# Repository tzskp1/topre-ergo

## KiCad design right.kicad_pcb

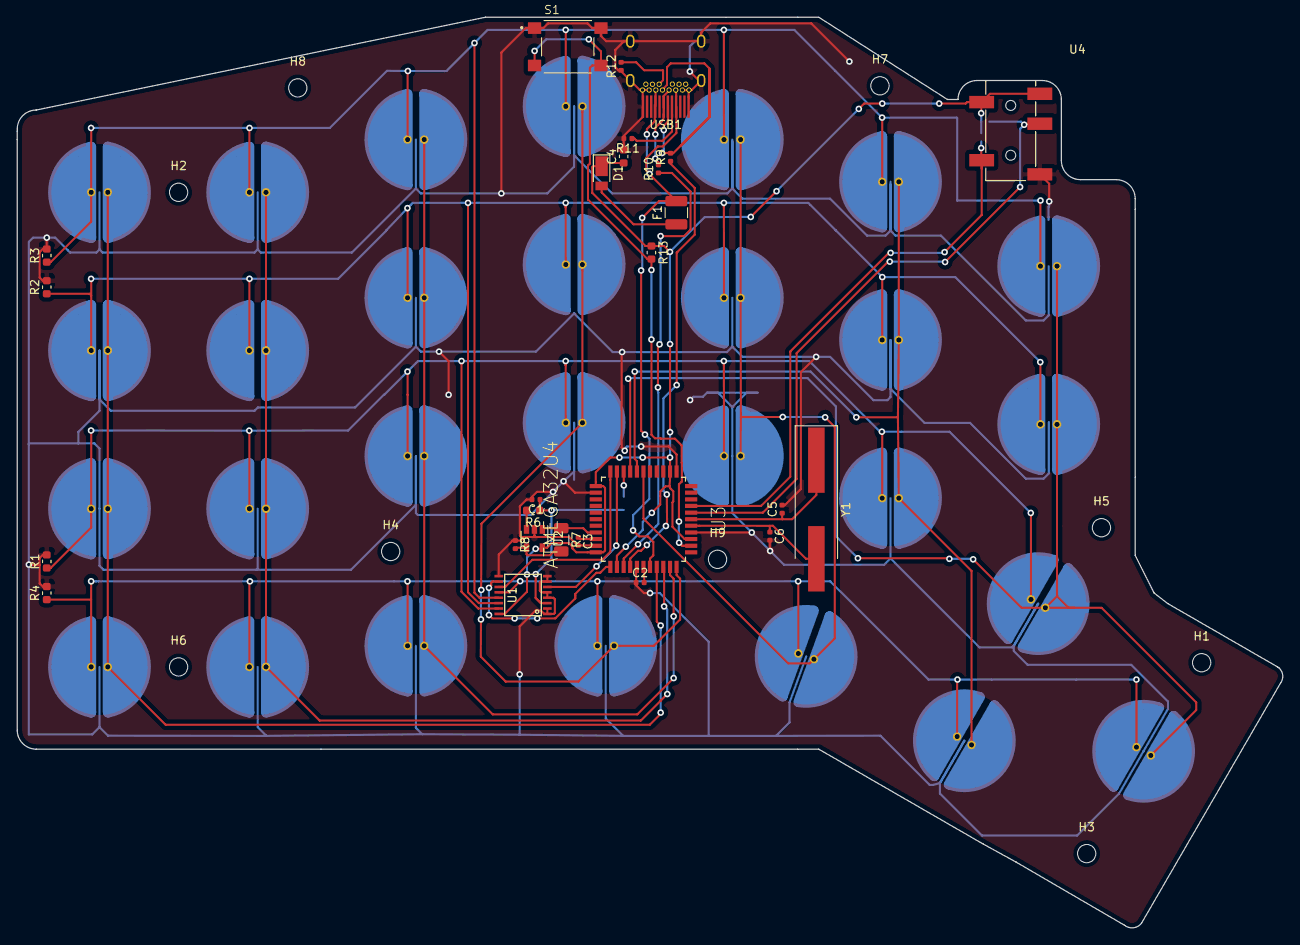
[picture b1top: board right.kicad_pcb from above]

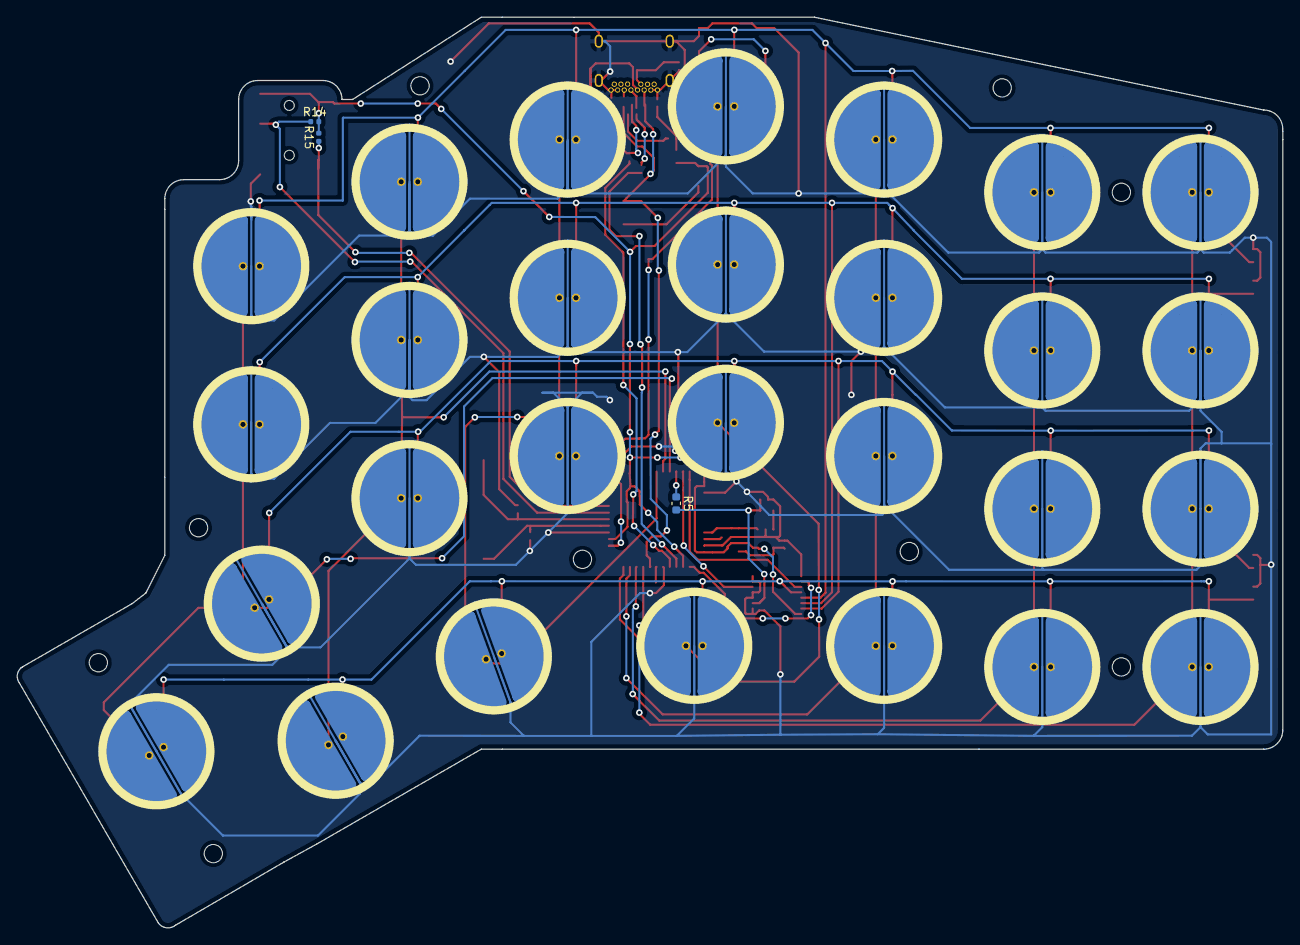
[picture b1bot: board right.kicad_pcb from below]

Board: 2 copper layers, 152.4 x 109.7 mm, 67 parts (3 on the bottom side), 36 nets.

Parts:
C1: 1n; R_0402_1005Metric
C2: 1u; C_0402_1005Metric
C3: 0.1u; C_0402_1005Metric
C4: 10u; C_0603_1608Metric
C5, C6: 22p; C_0402_1005Metric
D1: 1A; D_PowerDI-123
F1: 500m; Fuse_1210_3225Metric
H1, H2, H3, H4, H5, H6, H7, H8, H9: MountingHole; MountingHole_2.2mm_M2
R1, R2, R3, R4: 22k; R_0603_1608Metric
R5: 1k; R_0603_1608Metric
R6: 330; R_0603_1608Metric
R7: 56k; R_1206_3216Metric
R8: 270; R_0402_1005Metric
R9, R10: 22; R_0402_1005Metric
R11, R12, R14, R15: 5.1k; R_0402_1005Metric
R13: 10k; R_0603_1608Metric
S1: B3FS-1010P; SW_B3FS-1010P
TP1, TP2, TP3, TP4, TP5, TP6, TP7, TP8, TP9, TP10, TP11, TP12, TP13, TP14, TP15, TP16, TP17, TP18, TP19, TP20, TP21, TP22, TP23, TP24, TP25, TP26, TP27, TP28: ToprePad
U1: 74VHC4051AFT; TSSOP16
U2: GS8051-TR; SOT-23-5
U3: ATMEGA32U4; ATmega32U4
U4: PJ-327A
USB1: Wurth-632723300011; Wurth-632723300011-HandSoldering
Y1: Crystal; Crystal_SMD_HC49-SD_HandSoldering

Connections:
D+: R9.1, U3.4
D-: R10.1, U3.3
GND: C1.2, C2.1, C3.2, C4.2, C5.2, C6.2, R1.2, R2.2, R3.2, R4.2, R8.1, R11.2, R12.1, S1.1, S1.2, TP1.3, TP2.3, TP3.3, TP4.3, TP5.3, TP6.3, TP7.3, TP8.3, TP9.3, TP10.3, TP11.3, TP12.3, TP13.3, TP14.3, TP15.3, TP16.3, TP17.3, TP18.3, TP19.3, TP20.3, TP21.3, TP22.3, TP23.3, TP24.3, TP25.3, TP26.3, TP27.3, TP28.3, U1.1, U1.2, U1.4, U1.5, U1.7, U1.8, U1.9, U2.2, U3.5, U3.15, U3.23, U3.35, U3.43, U4.6, USB1.1, USB1.12, USB1.13, USB1.24, USB1.25, USB1.26
unnamed: C2.2, U3.6
unnamed: C3.1, U3.42
unnamed: C5.1, U3.17, Y1.1
unnamed: C6.1, U3.16, Y1.2
unnamed: D1.2, F1.1
unnamed: R6.2, U2.3
unnamed: R7.2, R8.2, U2.4
unnamed: R9.2, USB1.6, USB1.18
unnamed: R10.2, USB1.7, USB1.19
unnamed: R11.1, USB1.5
unnamed: R12.2, USB1.17
unnamed: R13.2, S1.3, S1.4, U3.13
VBUS: F1.2, U3.7, USB1.4, USB1.9, USB1.16, USB1.21
VCC: C4.1, D1.1, R13.1, R14.2, R15.2, U1.16, U2.5, U3.2, U3.14, U3.24, U3.34, U3.44, U4.3, U4.4
col0: TP1.1, TP2.1, TP3.1, TP4.1, U3.8
col1: TP5.1, TP6.1, TP7.1, TP8.1, U3.9
col2: TP9.1, TP10.1, TP11.1, TP12.1, U3.10
col3: TP13.1, TP14.1, TP15.1, TP16.1, U3.11
col4: TP17.1, TP18.1, TP19.1, TP20.1, U3.28
col5: TP21.1, TP22.1, TP23.1, TP24.1, U3.29
col6: TP25.1, TP26.1, TP27.1, TP28.1, U3.30
drain: R5.1, U3.31
inh: U1.6, U3.32
read: R7.1, U2.1, U3.41
row: C1.1, R5.2, R6.1, U1.3
row0: R3.1, TP1.2, TP5.2, TP9.2, TP13.2, TP17.2, TP21.2, TP25.2, U1.13
row1: R2.1, TP2.2, TP6.2, TP10.2, TP14.2, TP18.2, TP22.2, TP26.2, U1.14
row2: R1.1, TP3.2, TP7.2, TP11.2, TP15.2, TP19.2, TP23.2, TP27.2, U1.15
row3: R4.1, TP4.2, TP8.2, TP12.2, TP16.2, TP20.2, TP24.2, TP28.2, U1.12
scl: R14.1, U3.18, U4.5
sda: R15.1, U3.19, U4.2
sela: U1.11, U3.33
selb: U1.10, U3.1

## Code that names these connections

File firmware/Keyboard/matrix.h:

#ifndef matrix_h
#define matrix_h
  #include <avr/io.h>
  #include <avr/interrupt.h>

  #define DRAIN 6 /* C */
  #define INH   7 /* D */
  #define READ  4 /* F */
  #define SELA  2 /* D */
  #define SELB  6 /* E */

  #define ACTUATION  200
  #define RELEASE    100

  struct state {
    uint8_t depth;
    uint8_t pressed;
  };

  extern struct state states[4][7];

  void init_matrix (void);

  uint16_t diff_upto16 (uint16_t a, uint16_t b);

  uint16_t strobe_read (int row, int col);

  void scan_matrix (void);
#endif

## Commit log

2020-04-17 init
2020-04-17 drill
2020-04-17 add a jack
2020-04-17 add zone
2020-04-17 clean up & add script
2020-04-18 add holes
2020-04-18 improve
2020-04-19 3d -> 2d
2020-04-25 clean up
2020-04-25 fix array
2020-04-26 fix to reset
2020-04-26 before autoroute
2020-04-27 sloppy version
2020-04-27 add nc
2020-04-27 minor change
2020-04-27 test
2020-04-28 fix to expand gnd
2020-04-29 add left
2020-04-29 filled
2020-04-29 more and more
2020-04-29 minor
2020-05-06 add pull up
2020-05-06 fill
2020-05-08 twi master
2020-05-08 add matrix module
2020-05-09 ab keyboard
2020-05-09 sloppy fixhh
2020-05-21 fix holes
2020-05-21 update firmware
2020-05-21 add left topplate
2020-05-22 add right top plate
2020-06-03 fix jack
